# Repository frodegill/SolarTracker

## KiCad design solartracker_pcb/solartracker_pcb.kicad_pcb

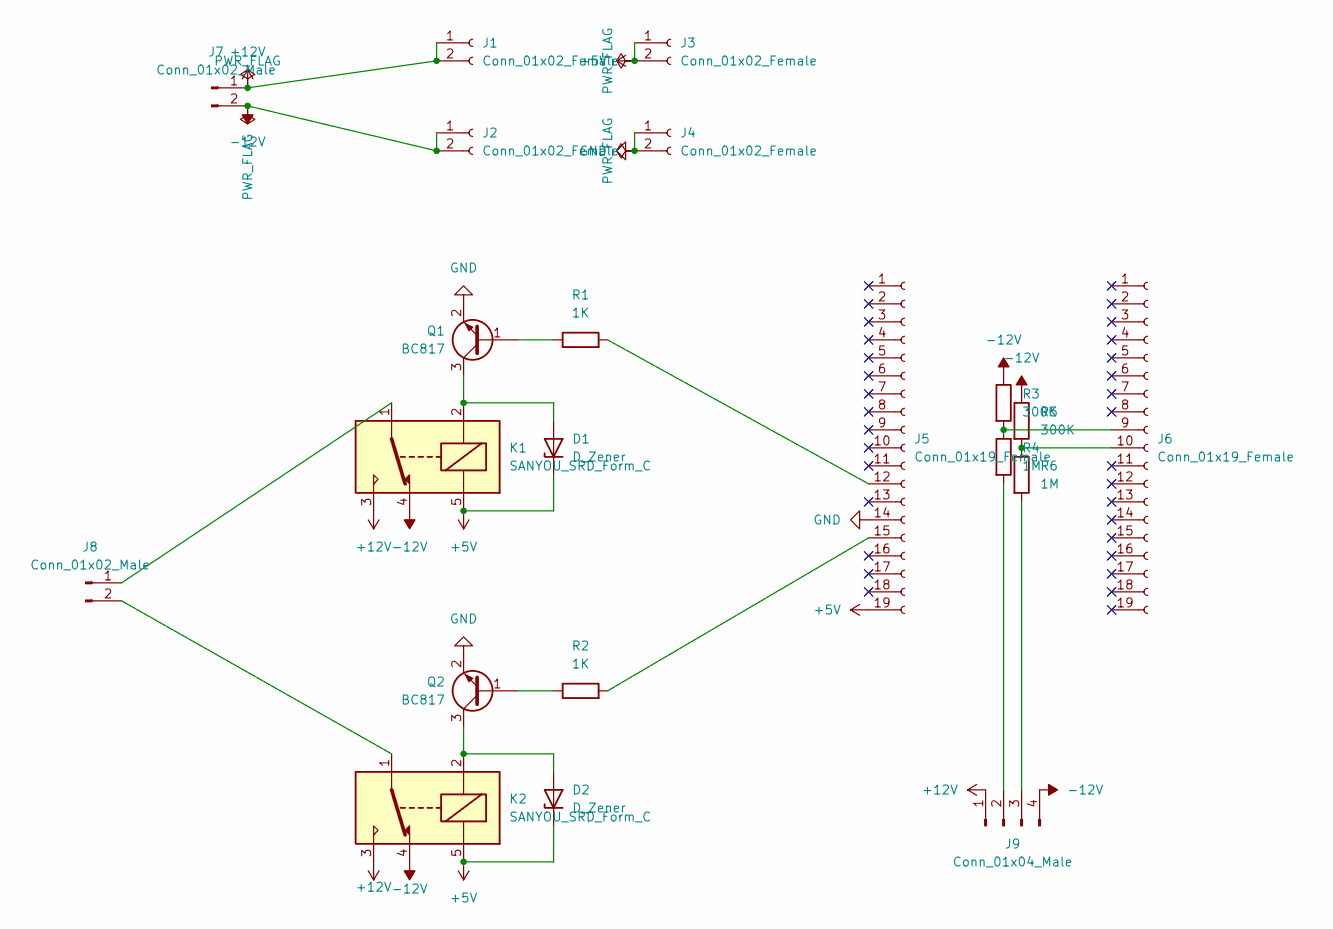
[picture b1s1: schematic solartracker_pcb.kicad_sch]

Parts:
D1, D2: D_Zener; D_SMB
J1, J2, J3, J4: Conn_01x02_Female; PinHeader_1x02_P2.54mm_Vertical
J5, J6: Conn_01x19_Female; PinHeader_1x19_P2.54mm_Vertical
J7, J8: Conn_01x02_Male; TerminalBlock_bornier-2_P5.08mm
J9: Conn_01x04_Male; TerminalBlock_bornier-4_P5.08mm
K1, K2: SANYOU_SRD_Form_C; Relay_SPDT_SANYOU_SRD_Series_Form_C
Q1, Q2: BC817; SOT-23
R1, R2: 1K; R_1206_3216Metric
R3, R5: 300K; R_1206_3216Metric
R4, R6: 1M; R_1206_3216Metric

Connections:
+5V: D1.1 (K), D2.1 (K), J3.1, J3.2, J5.19, K1.5, K2.5
+12V: J1.1, J1.2, J7.1, J9.1, K1.3, K2.3
-12V: J2.1, J2.2, J7.2, J9.4, K1.4, K2.4, R3.1, R5.1
GND: J4.1, J4.2, J5.14, Q1.2 (E), Q2.2 (E)
unnamed: D1.2 (A), K1.2, Q1.3 (C)
unnamed: D2.2 (A), K2.2, Q2.3 (C)
unnamed: J5.12, R1.2
unnamed: J5.15, R2.2
unnamed: J6.9, R3.2, R4.1
unnamed: J6.10, R5.2, R6.1
unnamed: J8.1, K1.1
unnamed: J8.2, K2.1
unnamed: J9.2, R4.2
unnamed: J9.3, R6.2
unnamed: Q1.1 (B), R1.1
unnamed: Q2.1 (B), R2.1

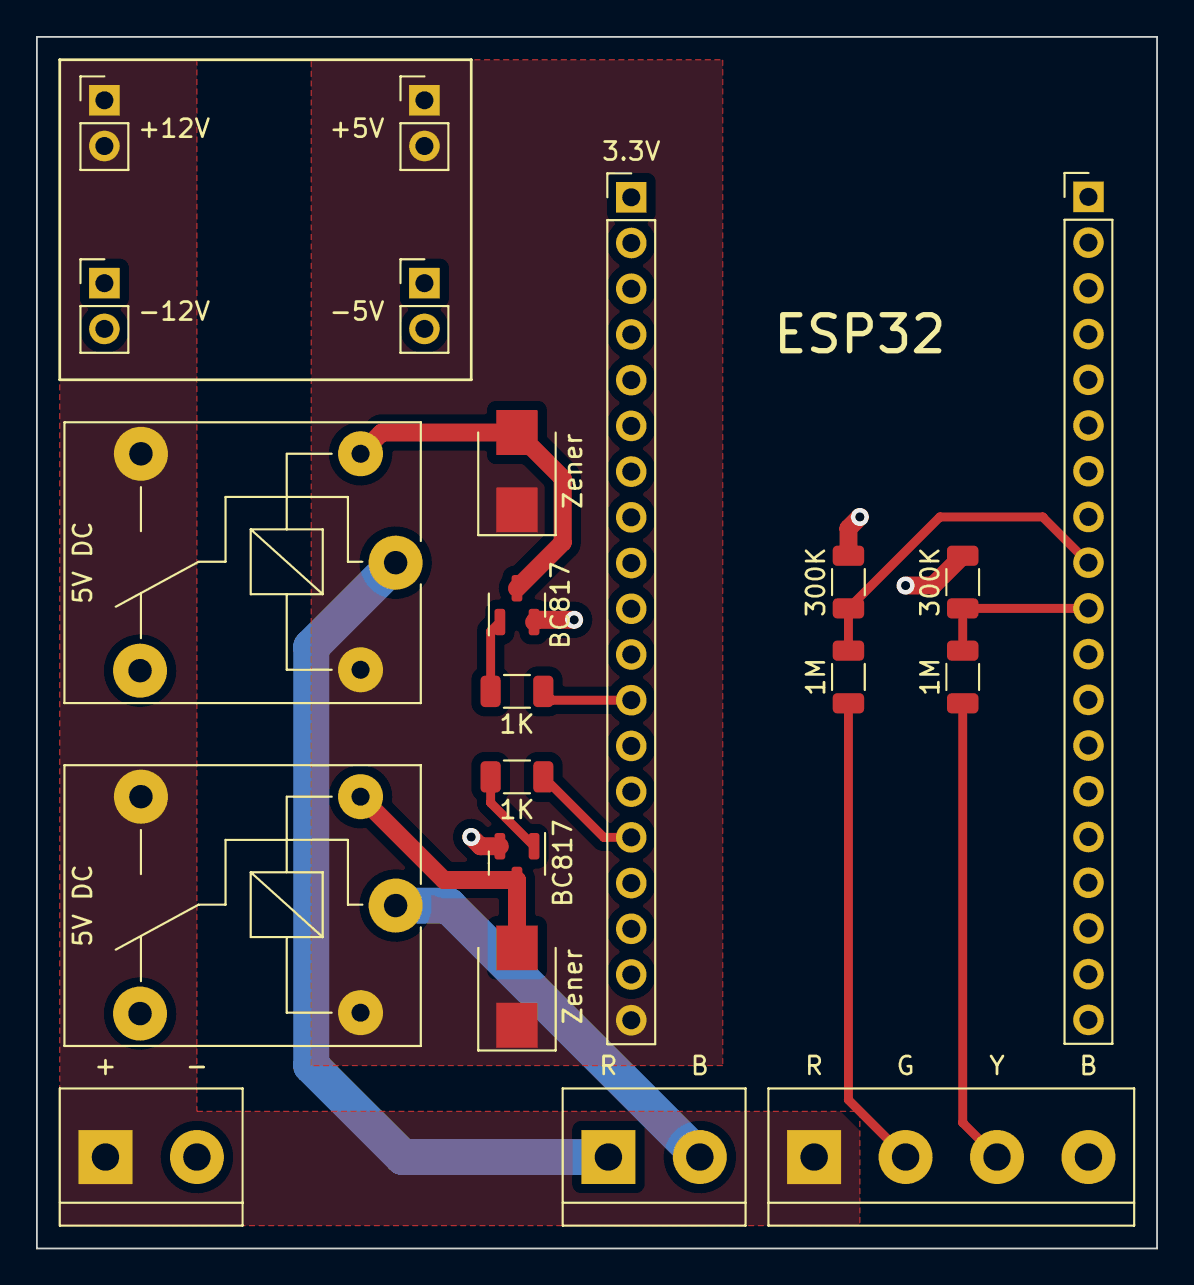
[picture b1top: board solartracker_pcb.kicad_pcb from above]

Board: 2 copper layers, 62.2 x 67.3 mm, 21 parts (0 on the bottom side), 16 nets.

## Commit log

2023-12-08 Added schematics, PCB and gerber files
